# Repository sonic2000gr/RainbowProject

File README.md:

<h1>The Rainbow Z80 Project</h1>

<h2>English Version</h2>

This repository contains schematics and info on the Rainbow Project.
This is a long overdue (27 years!) project to create a  Z80 based educational computer. It is inspired by the home micros of the 80s
that used the popular 8bit processor from Zilog.

The Rainbow Project machine planned initial specs are:

<ul>
<li>Z80 CPU with variable clock (0 Hz to maybe 2-4 MHz)</li>
<li>8KB EEPROM hosting monitor / test programs</li>
<li>2KB of static RAM</li>
<li>LCD 20 characters by 4 rows or similar</li>
<li>Status LEDs for all buses (Data, Address, Control)</li>
<li>Possibly HEX keypad for entering opcodes / data</li>
<li>Other features that will come by while experimenting!</li>
</ul>

<h2>Greek Version</h2>

Το παρόν repository περιέχει σχηματικά και πληροφορίες για το Rainbow Project
Το Rainbow Project είναι ένα έργο που έχει αργήσει *μόνο* 27 χρόνια! Άρχισα να το σχεδιάζω το 1990 και πολλά από τα εξαρτήματα του (CPU, RAM)
είχαν αγοραστεί τότε. Τελικά θα πραγματοποιηθεί ως Project του <a href="http://www.schoolspace.gr">SchoolSpace</a> το σχολικό έτος 2017-2018.
Το Rainbow Project είναι εμπνευσμένο από τα πολλά μηχανήματα της δεκαετίας του 80 που βασίζονταν στο δημοφιλή επεξεργαστή Z80 της Zilog.
Χαρακτηριστικά παραδείγματα: 

<ul>
<li>Siclair ZX80 / ZX81 / Spectrum</li>
<li>Amstrad CPC</li>
<li>MSX</li>
</ul>

Οι αρχικές προδιαγραφές του μηχανήματος (θα μεταβληθούν στην πορεία):

<ul>
<li>Επεξεργαστής Z80 με μεταβλητό ρολόι (από 0 Hz ως ίσως 2 ή 4 MHz)</li>
<li>8KB EEPROM με πρόγραμμα monitor και demos / tests</li>
<li>2KB Static RAM</li>
<li>Οθόνη LCD 20X4 η παρόμοια (με οδήγηση από Arduino ή MSP430)</li>
<li>Φωτεινές ενδείξεις με LEDs για όλους τους διαύλους. Το μηχάνημα θα χρησιμοποιείται για εκπαιδευτικούς σκοπούς και θα μπορεί να δείχνει
τα βήματα ανάκλησης / εκτέλεσης εντολών</li>
<li>Πληκτρολόγιο HEX για opcodes / data</li>
<li>Ότι άλλη ιδέα μας έρθει στο μεταξύ!</li>
</ul>

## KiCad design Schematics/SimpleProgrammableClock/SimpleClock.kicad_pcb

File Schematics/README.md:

This directory contains schematics in KiCad for the Z80 Rainbow Project

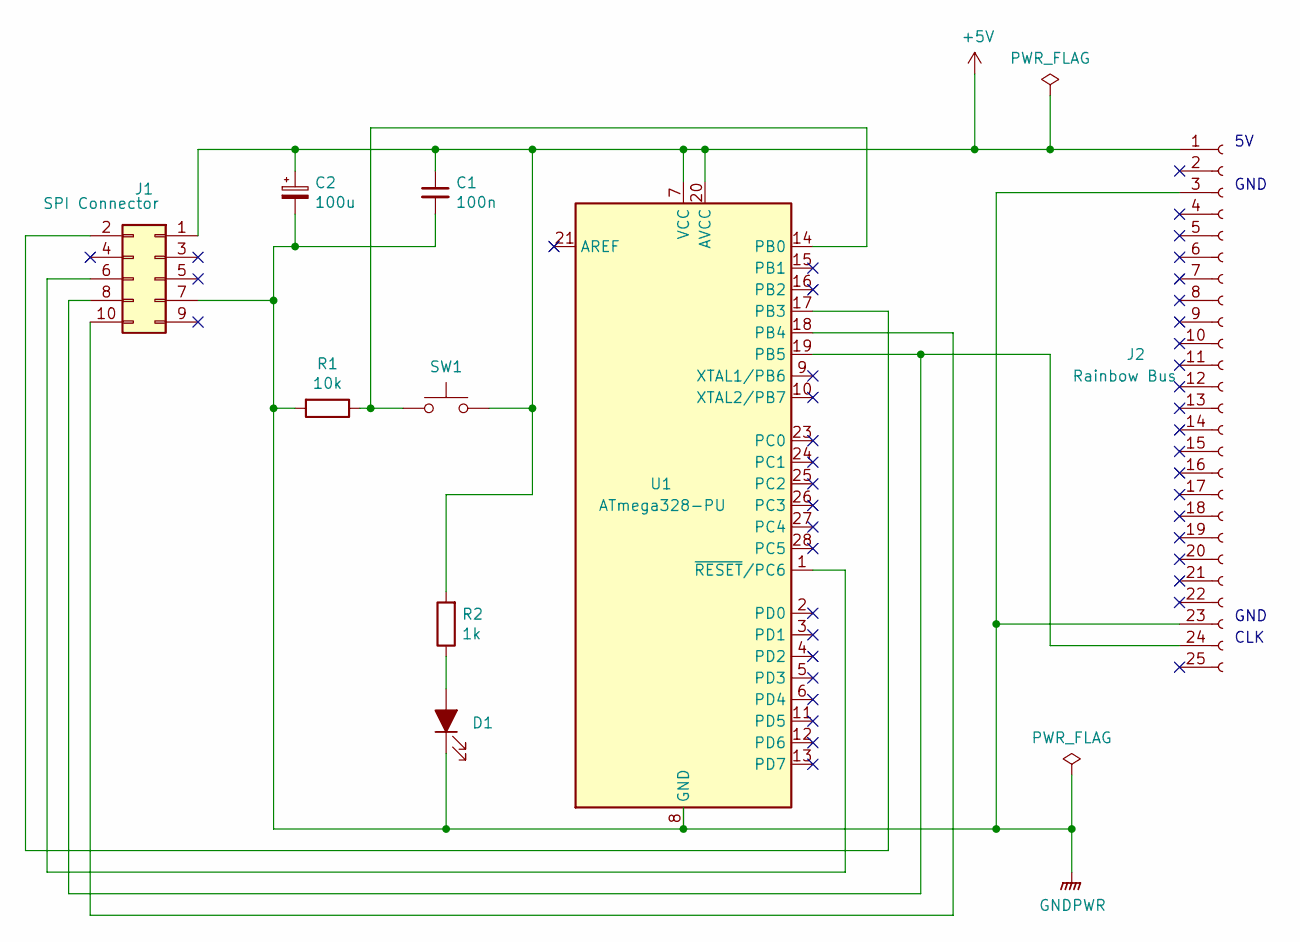
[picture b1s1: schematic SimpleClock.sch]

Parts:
C1: 100n; C_Disc_D5.1mm_W3.2mm_P5.00mm
C2: 100u; CP_Radial_D8.0mm_P3.50mm
D1: LED_ALT; D_DO-15_P12.70mm_Horizontal
J1: SPI Connector; PinHeader_2x05_P2.54mm_Vertical
J2: Rainbow Bus; PinHeader_1x25_P2.54mm_Vertical
R1: 10k; R_Axial_DIN0207_L6.3mm_D2.5mm_P10.16mm_Horizontal
R2: 1k; R_Axial_DIN0207_L6.3mm_D2.5mm_P10.16mm_Horizontal
SW1: SW; SW_PUSH_6mm_H4.3mm
U1: ATmega328-PU; DIP-28_W7.62mm

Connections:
+5V: C1.1, C2.1, J1.1, J2.1, R2.2, SW1.2, U1.7 (VCC), U1.20 (AVCC)
GNDPWR: C1.2, C2.2, D1.1 (K), J1.7, J2.3, J2.23, R1.2, U1.8 (GND), U1.22 (GND)
unnamed: D1.2 (A), R2.1
unnamed: J1.2, U1.17 (PB3)
unnamed: J1.6, U1.1 (~RESET~/PC6)
unnamed: J1.8, J2.24, U1.19 (PB5)
unnamed: J1.10, U1.18 (PB4)
unnamed: R1.1, SW1.1, U1.14 (PB0)

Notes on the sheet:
CLK
GND

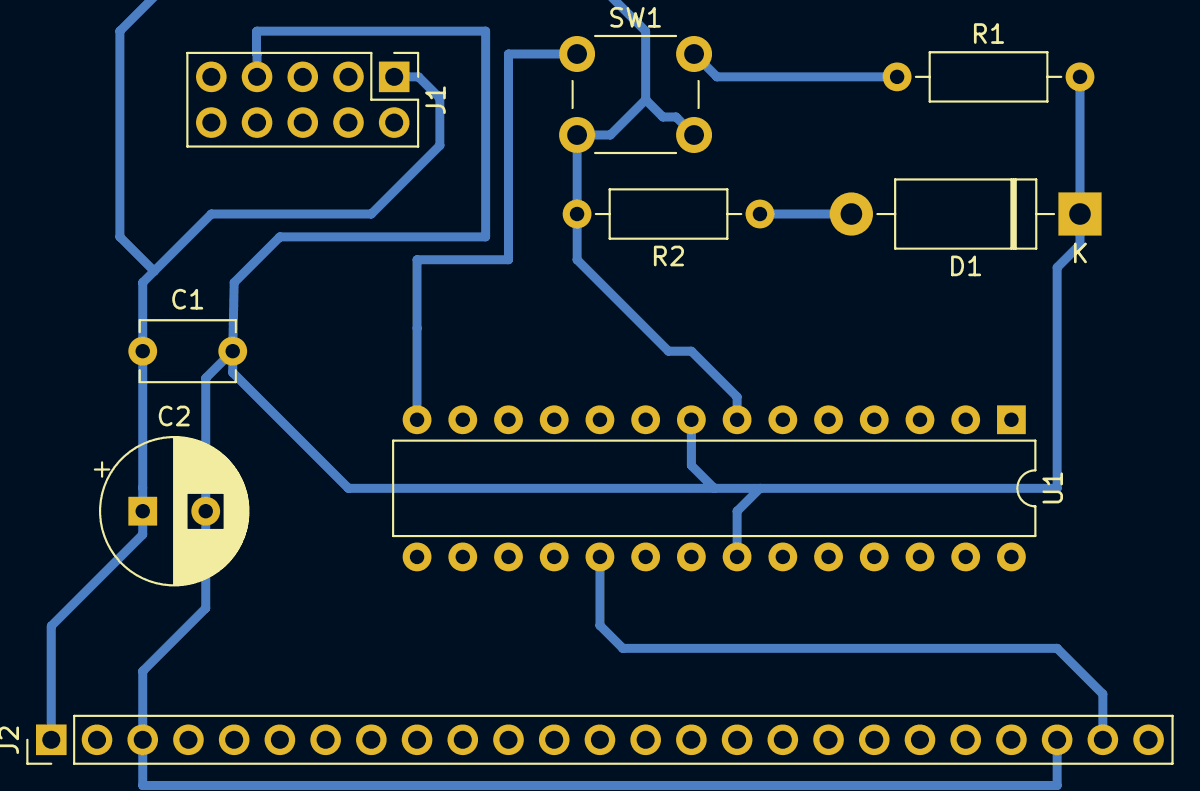
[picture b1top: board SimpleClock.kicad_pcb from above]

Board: 2 copper layers, 9 parts (0 on the bottom side), 8 nets.

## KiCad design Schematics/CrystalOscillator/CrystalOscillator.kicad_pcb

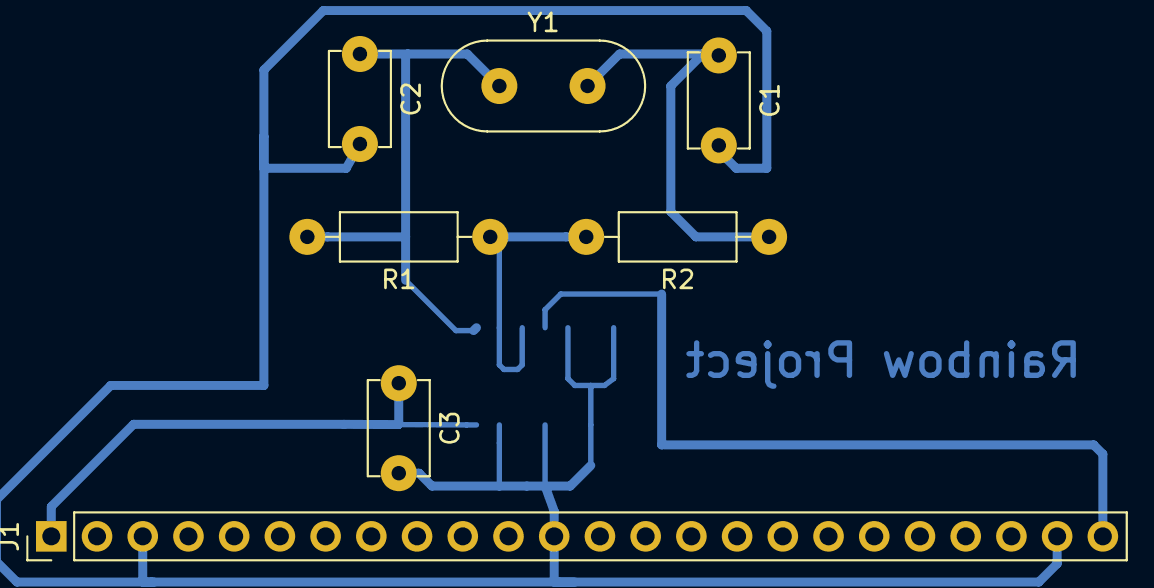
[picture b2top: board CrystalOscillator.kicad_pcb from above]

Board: 2 copper layers, 8 parts (1 on the bottom side), 6 nets.

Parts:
C1, C2: 3.3p; C_Disc_D5.1mm_W3.2mm_P5.00mm
C3: 0.1u; C_Disc_D5.1mm_W3.2mm_P5.00mm
J1: Conn_01x24_Female; PinHeader_1x24_P2.54mm_Vertical
R1: 1M; R_Axial_DIN0207_L6.3mm_D2.5mm_P10.16mm_Horizontal
R2: 10k; R_Axial_DIN0207_L6.3mm_D2.5mm_P10.16mm_Horizontal
U1: 74HC14; SOIC-14_3.9x8.7mm_P1.27mm
Y1: 4MHz Crystal; Crystal_HC18-U_Vertical

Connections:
GND: C1.2, C2.2, C3.2, J1.3, J1.12, J1.23, U1.5, U1.7, U1.9, U1.11, U1.13
unnamed: C1.1, R2.1, Y1.2
unnamed: C2.1, R1.2, U1.1, Y1.1
unnamed: J1.24, U1.4
unnamed: R1.1, R2.2, U1.2, U1.3
VCC: C3.1, J1.1, U1.14

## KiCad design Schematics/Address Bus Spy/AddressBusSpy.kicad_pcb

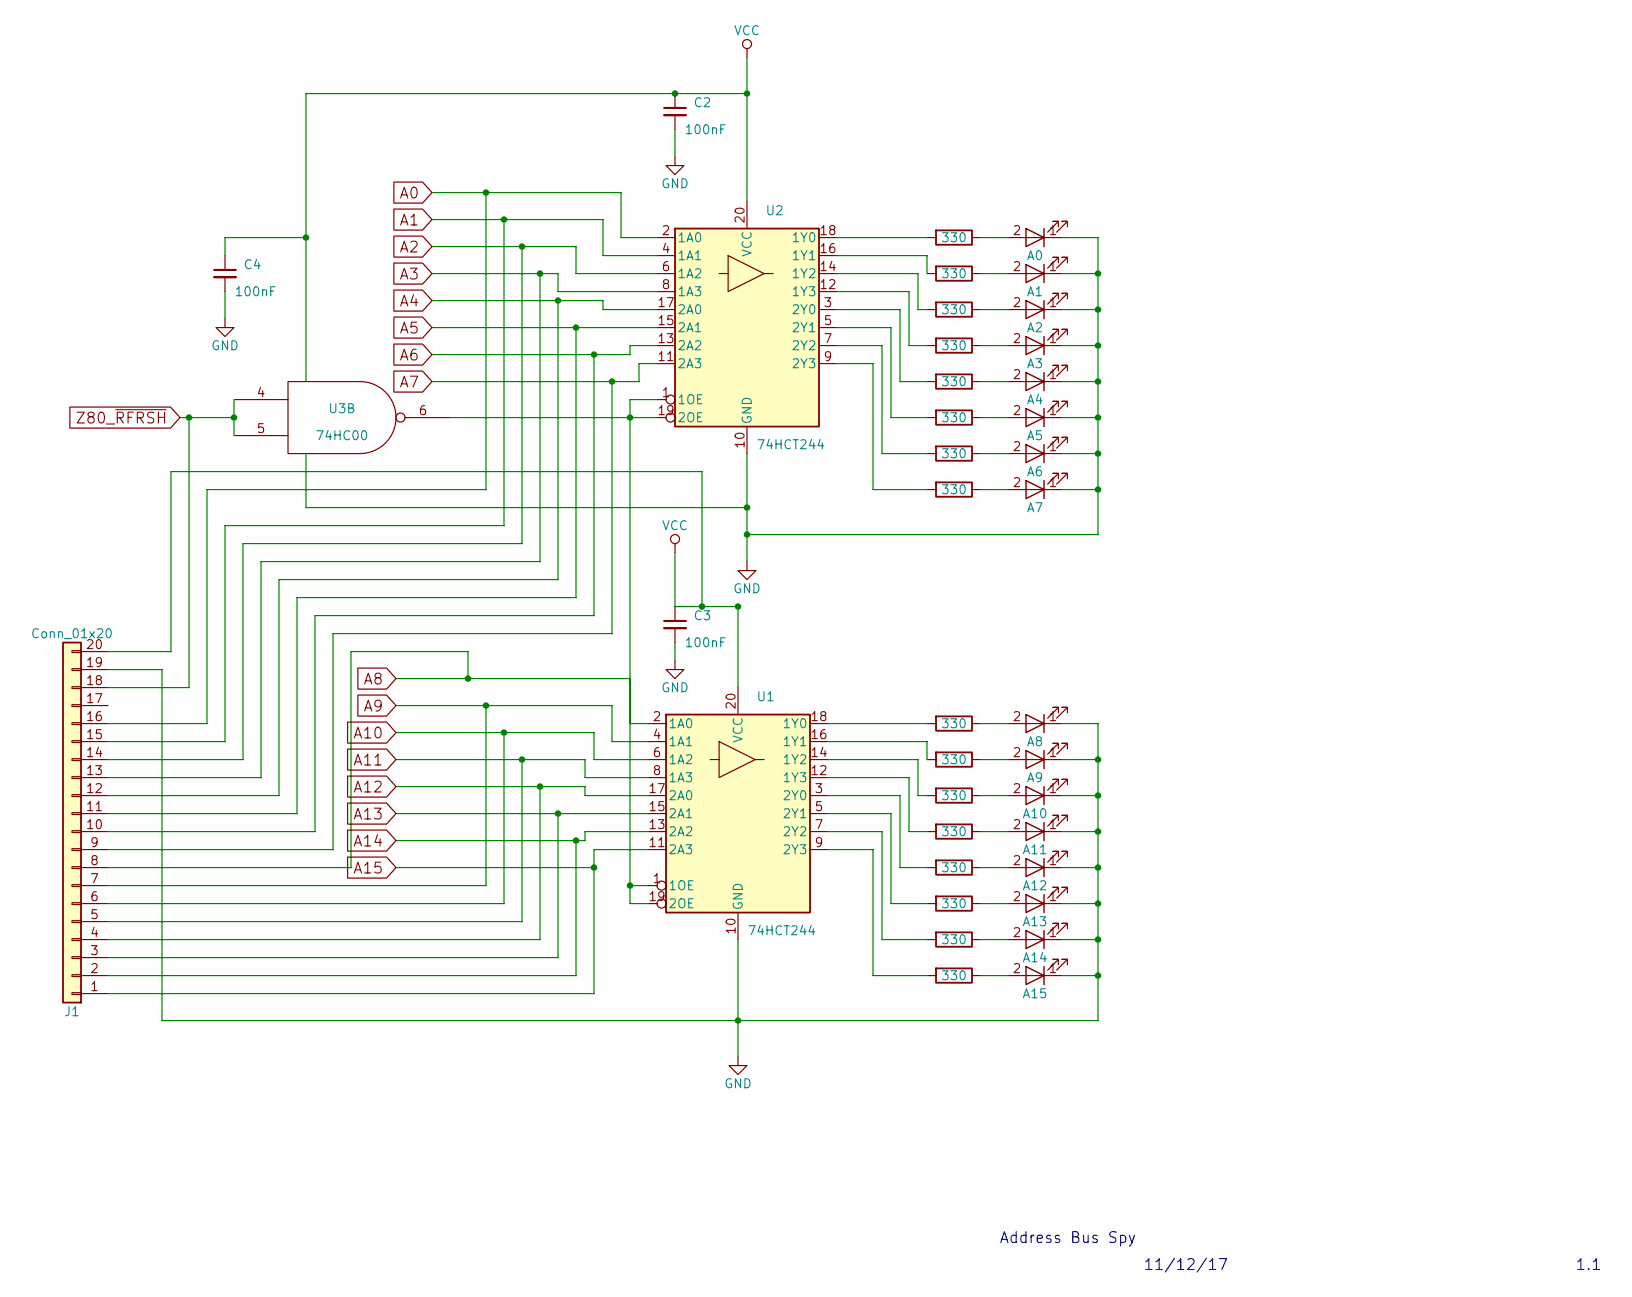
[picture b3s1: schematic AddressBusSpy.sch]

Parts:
A0, A1, A2, A3, A4, A5, A6, A7, A8, A9, A10, A11, A12, A13, A14, A15: LED; LED_thickpad
C2, C3, C4: 100nF; C_Disc_D10.0mm_W2.5mm_P5.00mm
J1: Conn_01x20; Pin_Header_Straight_1x20_Pitch2.54mm
R1, R2, R3, R4, R5, R6, R7, R8, R9, R10, R11, R12, R13, R14, R15, R16: 330; R_Axial_DIN0204_L3.6mm_D1.6mm_P7.62mm_Horizontal
U1, U2: 74HCT244; DIP-20_thickpad
U3: 74HC00; DIP-14_thickpad

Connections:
A0: J1.16, U2.2 (1A0)
A1: J1.15, U2.4 (1A1)
A2: J1.14, U2.6 (1A2)
A3: J1.13, U2.8 (1A3)
A4: J1.12, U2.17 (2A0)
A5: J1.11, U2.15 (2A1)
A6: J1.10, U2.13 (2A2)
A7: J1.9, U2.11 (2A3)
A8: J1.8, U1.2 (1A0)
A9: J1.7, U1.4 (1A1)
A10: J1.6, U1.6 (1A2)
A11: J1.5, U1.8 (1A3)
A12: J1.4, U1.17 (2A0)
A13: J1.3, U1.15 (2A1)
A14: J1.2, U1.13 (2A2)
A15: J1.1, U1.11 (2A3)
GND: A0.1 (K), A1.1 (K), A2.1 (K), A3.1 (K), A4.1 (K), A5.1 (K), A6.1 (K), A7.1 (K), A8.1 (K), A9.1 (K), A10.1 (K), A11.1 (K), A12.1 (K), A13.1 (K), A14.1 (K), A15.1 (K), C2.2, C3.2, C4.2, J1.19, U1.10 (GND), U2.10 (GND), U3.7 (GND)
unnamed: A0.2 (A), R1.1
unnamed: A1.2 (A), R2.1
unnamed: A2.2 (A), R3.1
unnamed: A3.2 (A), R4.1
unnamed: A4.2 (A), R5.1
unnamed: A5.2 (A), R6.1
unnamed: A6.2 (A), R7.1
unnamed: A7.2 (A), R8.1
unnamed: A8.2 (A), R9.1
unnamed: A9.2 (A), R10.1
unnamed: A10.2 (A), R11.1
unnamed: A11.2 (A), R12.1
unnamed: A12.2 (A), R13.1
unnamed: A13.2 (A), R14.1
unnamed: A14.2 (A), R15.1
unnamed: A15.2 (A), R16.1
unnamed: R1.2, U2.18 (1Y0)
unnamed: R2.2, U2.16 (1Y1)
unnamed: R3.2, U2.14 (1Y2)
unnamed: R4.2, U2.12 (1Y3)
unnamed: R5.2, U2.3 (2Y0)
unnamed: R6.2, U2.5 (2Y1)
unnamed: R7.2, U2.7 (2Y2)
unnamed: R8.2, U2.9 (2Y3)
unnamed: R9.2, U1.18 (1Y0)
unnamed: R10.2, U1.16 (1Y1)
unnamed: R11.2, U1.14 (1Y2)
unnamed: R12.2, U1.12 (1Y3)
unnamed: R13.2, U1.3 (2Y0)
unnamed: R14.2, U1.5 (2Y1)
unnamed: R15.2, U1.7 (2Y2)
unnamed: R16.2, U1.9 (2Y3)
unnamed: U1.1 (1OE), U1.19 (2OE), U2.1 (1OE), U2.19 (2OE), U3.6
VCC: C2.1, C3.1, C4.1, J1.20, U1.20 (VCC), U2.20 (VCC), U3.14 (VCC)
Z80_~RFRSH: J1.18, U3.4, U3.5

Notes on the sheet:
Address Bus Spy
11/12/17
1.1

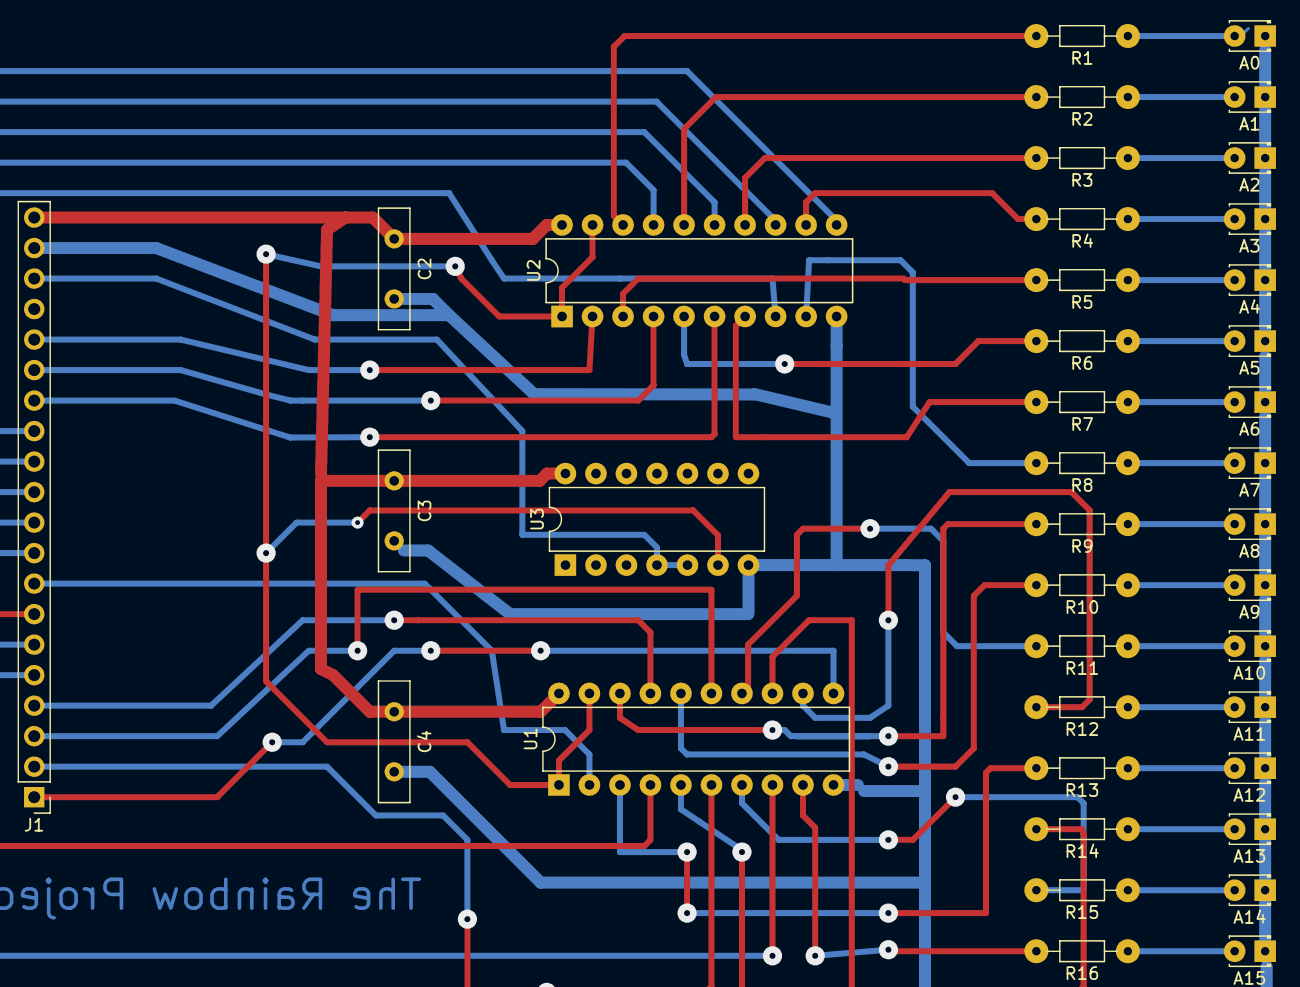
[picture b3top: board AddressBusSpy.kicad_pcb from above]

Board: 2 copper layers, 39 parts (0 on the bottom side), 52 nets.

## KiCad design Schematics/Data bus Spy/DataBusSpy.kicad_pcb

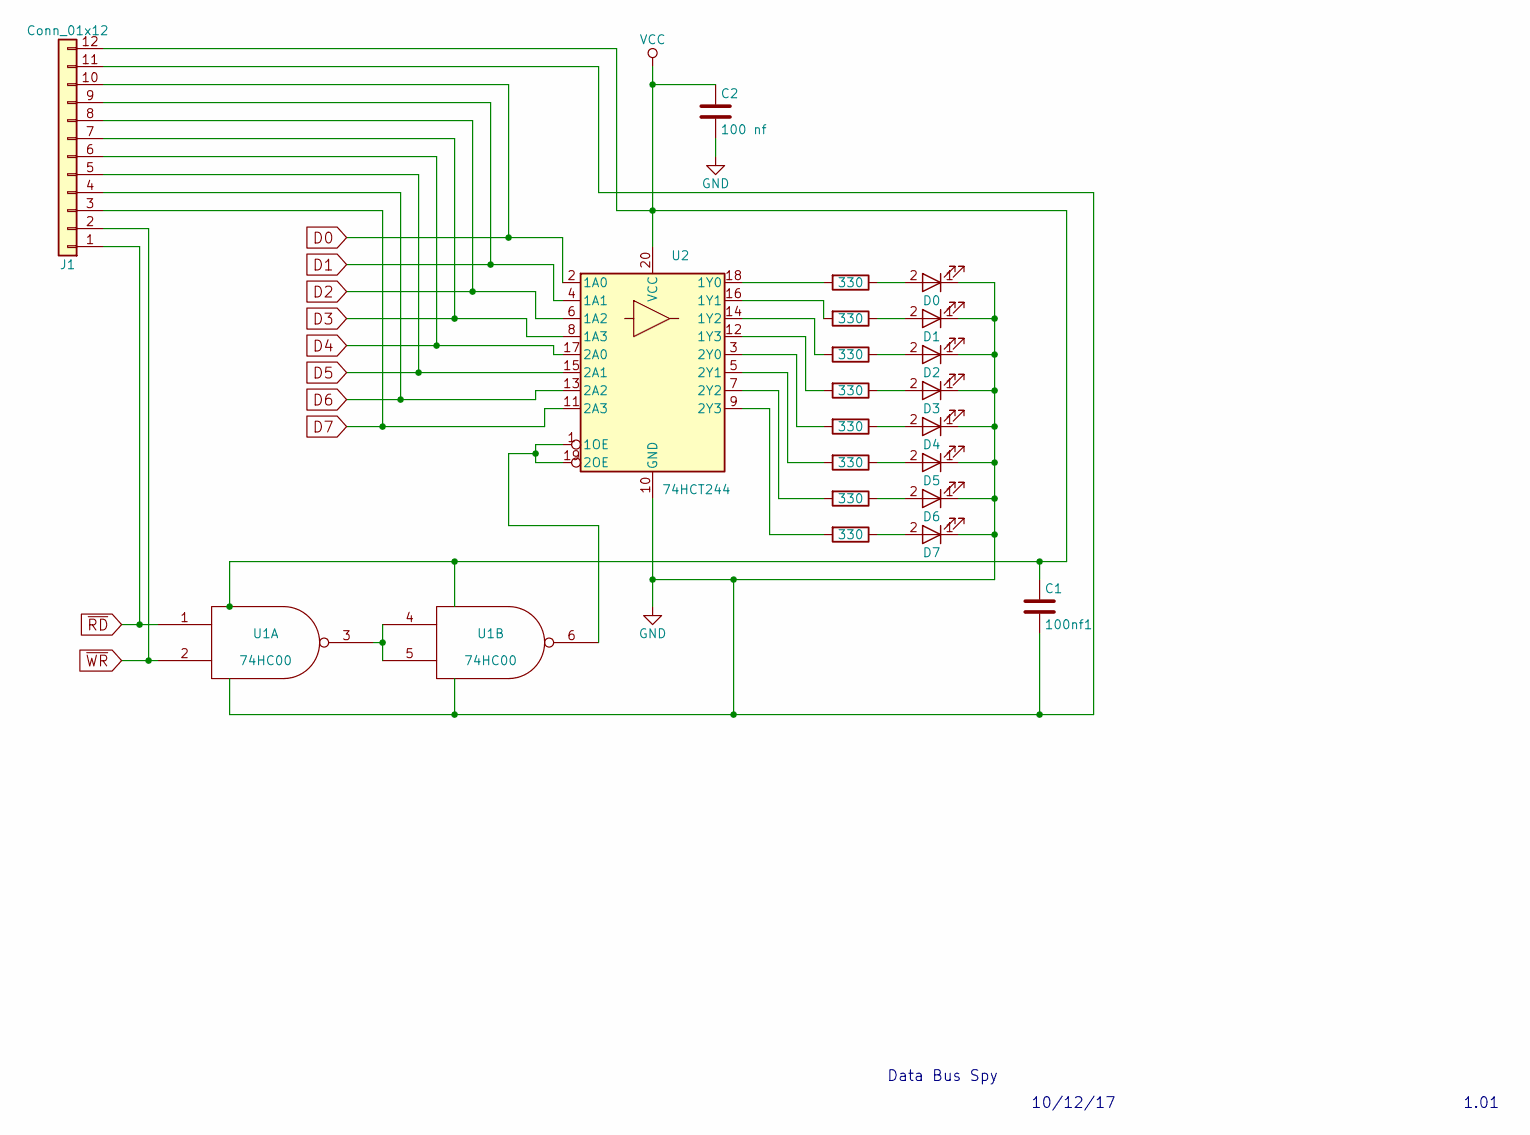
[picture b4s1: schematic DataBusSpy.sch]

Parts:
100nf1: C1; C_Disc_D10.0mm_W2.5mm_P5.00mm
C2: 100 nf; C_Disc_D10.0mm_W2.5mm_P5.00mm
D0, D1, D2, D3, D4, D5, D6, D7: LED; LED_thickpad
J1: Conn_01x12; Pin_Header_Straight_1x12_thickpad
R1, R2, R3, R4, R5, R6, R7, R8: 330; Resistor_thickpad
U1: 74HC00; DIP-14_thickpad
U2: 74HCT244; DIP-20_thickpad

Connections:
D0: J1.10, U2.2 (1A0)
D1: J1.9, U2.4 (1A1)
D2: J1.8, U2.6 (1A2)
D3: J1.7, U2.8 (1A3)
D4: J1.6, U2.17 (2A0)
D5: J1.5, U2.15 (2A1)
D6: J1.4, U2.13 (2A2)
D7: J1.3, U2.11 (2A3)
GND: 100nf1.1, C2.2, D0.1 (K), D1.1 (K), D2.1 (K), D3.1 (K), D4.1 (K), D5.1 (K), D6.1 (K), D7.1 (K), J1.11, U1.7 (GND), U2.10 (GND)
unnamed: D0.2 (A), R1.1
unnamed: D1.2 (A), R2.1
unnamed: D2.2 (A), R3.1
unnamed: D3.2 (A), R4.1
unnamed: D4.2 (A), R5.1
unnamed: D5.2 (A), R6.1
unnamed: D6.2 (A), R7.1
unnamed: D7.2 (A), R8.1
unnamed: R1.2, U2.18 (1Y0)
unnamed: R2.2, U2.16 (1Y1)
unnamed: R3.2, U2.14 (1Y2)
unnamed: R4.2, U2.12 (1Y3)
unnamed: R5.2, U2.3 (2Y0)
unnamed: R6.2, U2.5 (2Y1)
unnamed: R7.2, U2.7 (2Y2)
unnamed: R8.2, U2.9 (2Y3)
unnamed: U1.3, U1.4, U1.5
unnamed: U1.6, U2.1 (1OE), U2.19 (2OE)
VCC: 100nf1.2, C2.1, J1.12, U1.14 (VCC), U2.20 (VCC)
~RD: J1.1, U1.1
~WR: J1.2, U1.2

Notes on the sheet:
Data Bus Spy
10/12/17
1.01

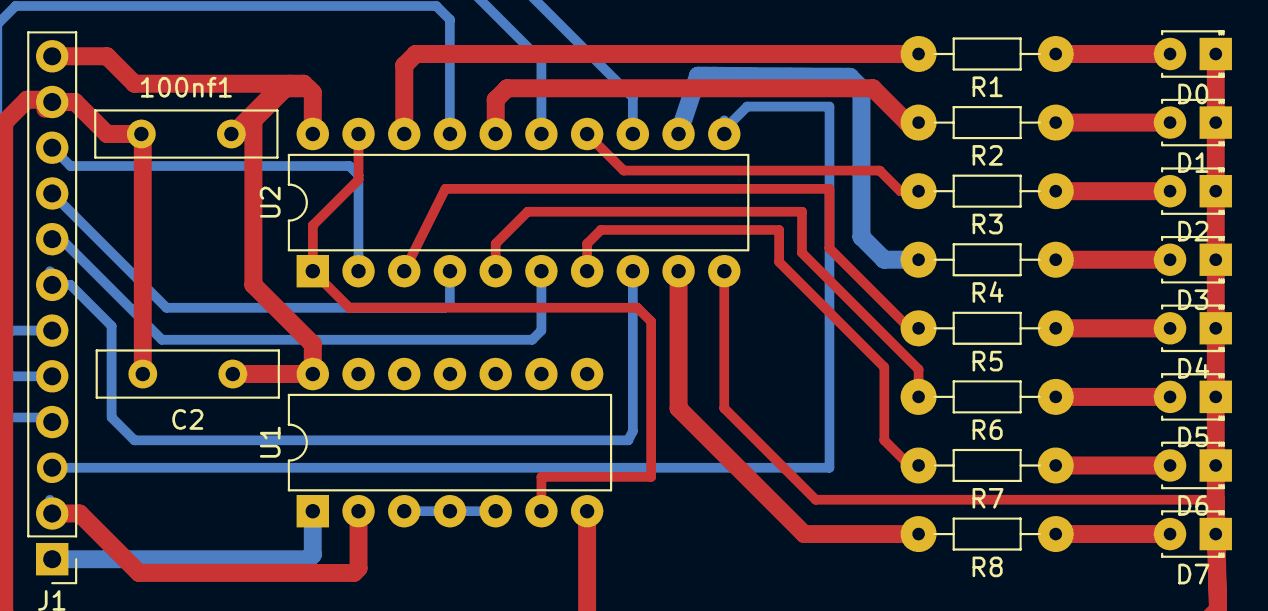
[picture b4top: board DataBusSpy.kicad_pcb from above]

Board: 2 copper layers, 21 parts (0 on the bottom side), 30 nets.

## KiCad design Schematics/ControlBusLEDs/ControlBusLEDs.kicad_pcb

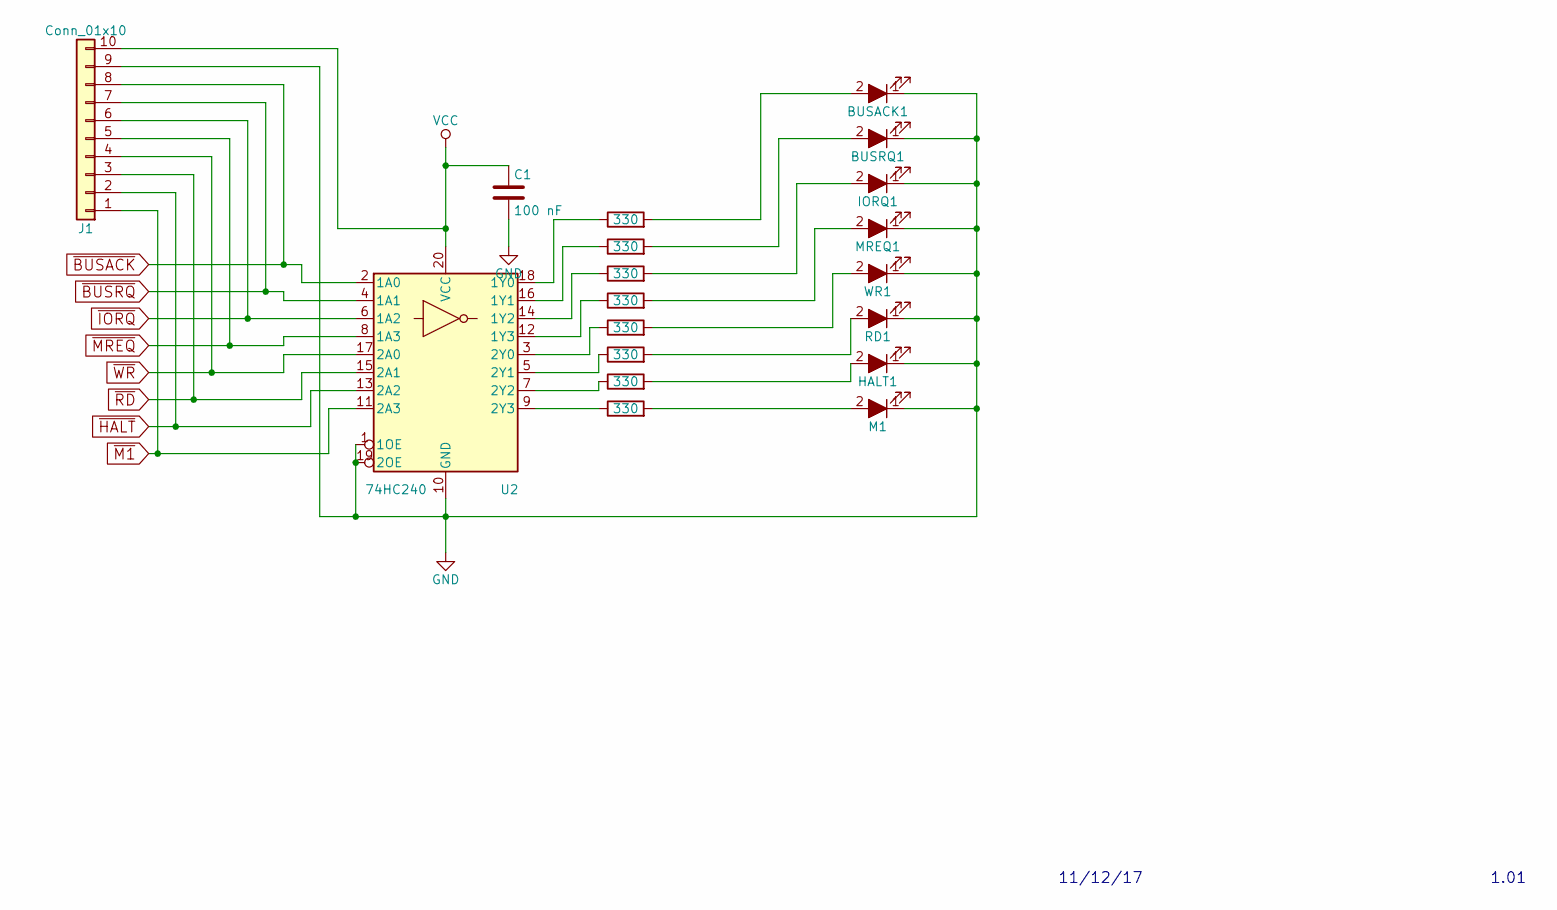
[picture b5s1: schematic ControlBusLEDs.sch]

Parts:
BUSACK1: LED_ALT; LED_D1.8mm_W3.3mm_H2.4mm
BUSRQ1: LED_ALT; LED_D1.8mm_W3.3mm_H2.4mm
C1: 100 nF; C_Disc_D10.0mm_W2.5mm_P5.00mm
HALT1: LED_ALT; LED_D1.8mm_W3.3mm_H2.4mm
IORQ1: LED_ALT; LED_D1.8mm_W3.3mm_H2.4mm
J1: Conn_01x10; Pin_Header_Straight_1x10_Pitch2.54mm
M1: LED_ALT; LED_D1.8mm_W3.3mm_H2.4mm
MREQ1: LED_ALT; LED_D1.8mm_W3.3mm_H2.4mm
R1, R2, R3, R4, R5, R6, R7, R8: 330; R_Axial_DIN0204_L3.6mm_D1.6mm_P7.62mm_Horizontal
RD1: LED_ALT; LED_D1.8mm_W3.3mm_H2.4mm
U2: 74HC240; DIP-20_W7.62mm
WR1: LED_ALT; LED_D1.8mm_W3.3mm_H2.4mm

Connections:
GND: BUSACK1.1 (K), BUSRQ1.1 (K), C1.2, HALT1.1 (K), IORQ1.1 (K), J1.9, M1.1 (K), MREQ1.1 (K), RD1.1 (K), U2.1 (1OE), U2.10 (GND), U2.19 (2OE), WR1.1 (K)
unnamed: BUSACK1.2 (A), R1.2
unnamed: BUSRQ1.2 (A), R2.2
unnamed: HALT1.2 (A), R7.2
unnamed: IORQ1.2 (A), R3.2
unnamed: M1.2 (A), R8.2
unnamed: MREQ1.2 (A), R4.2
unnamed: R1.1, U2.18 (1Y0)
unnamed: R2.1, U2.16 (1Y1)
unnamed: R3.1, U2.14 (1Y2)
unnamed: R4.1, U2.12 (1Y3)
unnamed: R5.1, U2.3 (2Y0)
unnamed: R5.2, WR1.2 (A)
unnamed: R6.1, U2.5 (2Y1)
unnamed: R6.2, RD1.2 (A)
unnamed: R7.1, U2.7 (2Y2)
unnamed: R8.1, U2.9 (2Y3)
VCC: C1.1, J1.10, U2.20 (VCC)
~BUSACK: J1.8, U2.2 (1A0)
~BUSRQ: J1.7, U2.4 (1A1)
~HALT: J1.2, U2.13 (2A2)
~IORQ: J1.6, U2.6 (1A2)
~M1: J1.1, U2.11 (2A3)
~MREQ: J1.5, U2.8 (1A3)
~RD: J1.3, U2.15 (2A1)
~WR: J1.4, U2.17 (2A0)

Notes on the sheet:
11/12/17
1.01

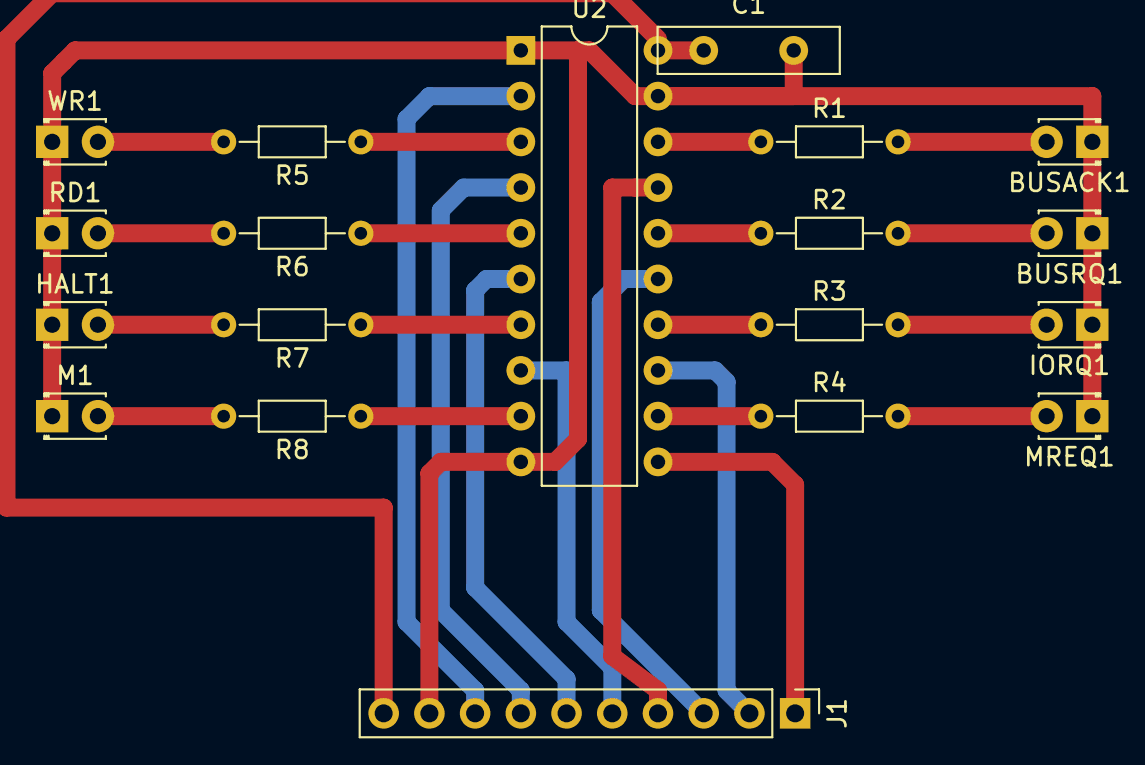
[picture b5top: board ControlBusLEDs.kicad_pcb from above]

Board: 2 copper layers, 19 parts (0 on the bottom side), 26 nets.

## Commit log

2017-12-10 Add initial schematics for Z80/ROM test circuits
2017-12-10 Create README.md
    Add some info on RainbowProject
2017-12-10 Add graphics folder with logos and artwork for RainbowProject
2017-12-10 Minor fixes in 74HC138 test schematic
2017-12-10 Minor nits in control bus LEDs schematic
2017-12-10 Add Data Bus Spy schematic
2017-12-10 Delete DataBusSpy.bak
    Delete unneeded backup file
2017-12-11 Slight changes in DataBus Spy
2017-12-11 Remove connector from ControlBusLEDs schematic. Add .gitignore
2017-12-11 Add initial version of Address Decoder
2017-12-11 Add initial version of Address Bus Spy
2017-12-14 Update ControlBusLEDs schematic and add initial PCB
2017-12-15 Add Data Bus Spy PCB and custom footprint library
2017-12-15 Add RAM test circuit (breadboard)
2017-12-17 Add PCB for Address Bus Spy schematic
2018-01-13 Add prelim version of display driver (MSP430G2553 code)
2018-01-15 Add initial version of IDI schematic
2018-01-23 Add preliminary Z80 mainboard schematics
2018-01-27 Add Rainbow Project logo rendered in HTML/CSS. Contributed by Konstantinos Kapenekakis
2018-02-03 Modified MSP430 display code just before adding LCD control code
2018-03-02 Final Version of IDI BIOS - Supports several commands
2018-03-09 Add a buffer stage for the IORQ signal in IDI - required for reliable operation
2018-03-12 Add second Rainbow Project logo, based on an idea by Nikos Koutsonikolis
2018-03-15 Add revision 1.1 of Z80 Mainboard
2018-03-20 Add initial version of programmable clock
2018-03-31 Add initial version of code for the ProgrammableClock system
2018-04-16 Add project posters (svg). Slightly modify project logo
2018-04-19 Add presentation for open day
2018-04-22 Add Z80 assembly source / binary for the Rainbow Project Demo
2018-09-24 Add initial versions of posters for MakerFaire Rome
2019-01-18 Update schematics to KiCad 5
2019-01-18 Add initial code and schematic for keyboard interface
2019-01-18 Minor changes in IO Decoder schematic
2019-01-21 Move IO Decoder to schematics and add Speaker and Joystick Ports
2019-01-21 Add soundcard initial schematic
2019-01-23 Save all Schematics again to overcome problems with version change
2019-03-04 Add schematic and PCB for 4MHz Crystal Oscillator
2019-03-05 Final version of 4 MHz clock PCB
2019-03-12 Redesign the sound card to use a bare Atmega 328P instead of arduino nano
2019-03-13 Add power flags to sound card schematic
2019-03-28 Add pygame code and logo for startup screen
2019-03-28 Add logo to python directory
2019-03-28 Add font files and modify python code to use them directly
2019-03-29 Write a second test screen / selection screen for displaypi
2019-03-29 - Modify Python program to prepare it for Z80 interfacing - Add a short demo in Z80 Assembly for DisplayPI
2019-03-31 Add a logo class to be used in the demo
2019-03-31 Add proof of concept test python script for Z80-RasPI communication
2019-03-31 Add displaypi schematic (Z80-RasPI Bus Interface)
2019-04-03 Redesign IO Decoder to include backplane
2019-04-03 Update gitignore
2019-04-04 Change connector layouts of IO Decoder to match existing Display port layout on main board
2019-04-08 Add preliminary code for soundcard
2019-04-08 Add initial (incomplete) version of quiz game in Z80 Assembly
2019-04-09 Add code for displaypi using RPi.GPIO
2019-04-10 Alter screen protocol in displaypi
2019-04-10 Various changes to Z80 assembly demo
2019-04-10 Small fixes in displaypi-pygame
2019-04-14 Add schematic and code for a simple programmable clock based on ATMega 328P
2019-04-15 Add a second version of the logic level converter for RasPI, using MOSFETs
2019-10-15 Add first revision of keyboard code (arduino mega)
